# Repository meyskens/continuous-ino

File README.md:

Continuous Ino - CI server for Arduino  
======================================

Continuous Ino is a CI software designed to run unit tests in Arduino based hardware using frameworks like [arduinounit](https://github.com/mmurdoch/arduinounit).  
Continuous Ino will upload the code from a GitHub repository, run the tests and even emulates components. Continuous Ino itself runs on a Raspberry Pi, using a special designed PCB it's GPIO pins power an Arduino (nano) and is able to send and receive to the Arduino's interfaces. Both analog and digital signals are supported. 

## Background
Continuous Ino is developed for an international collaboration between TH Köln and Thomas More Geel. Since we have never seen a solution like this we've decided to open source our work under the GPL License following Arduino itself.

## Project by
- Ben De Breuker
- Maartje Eyskens
- Kristie Lim

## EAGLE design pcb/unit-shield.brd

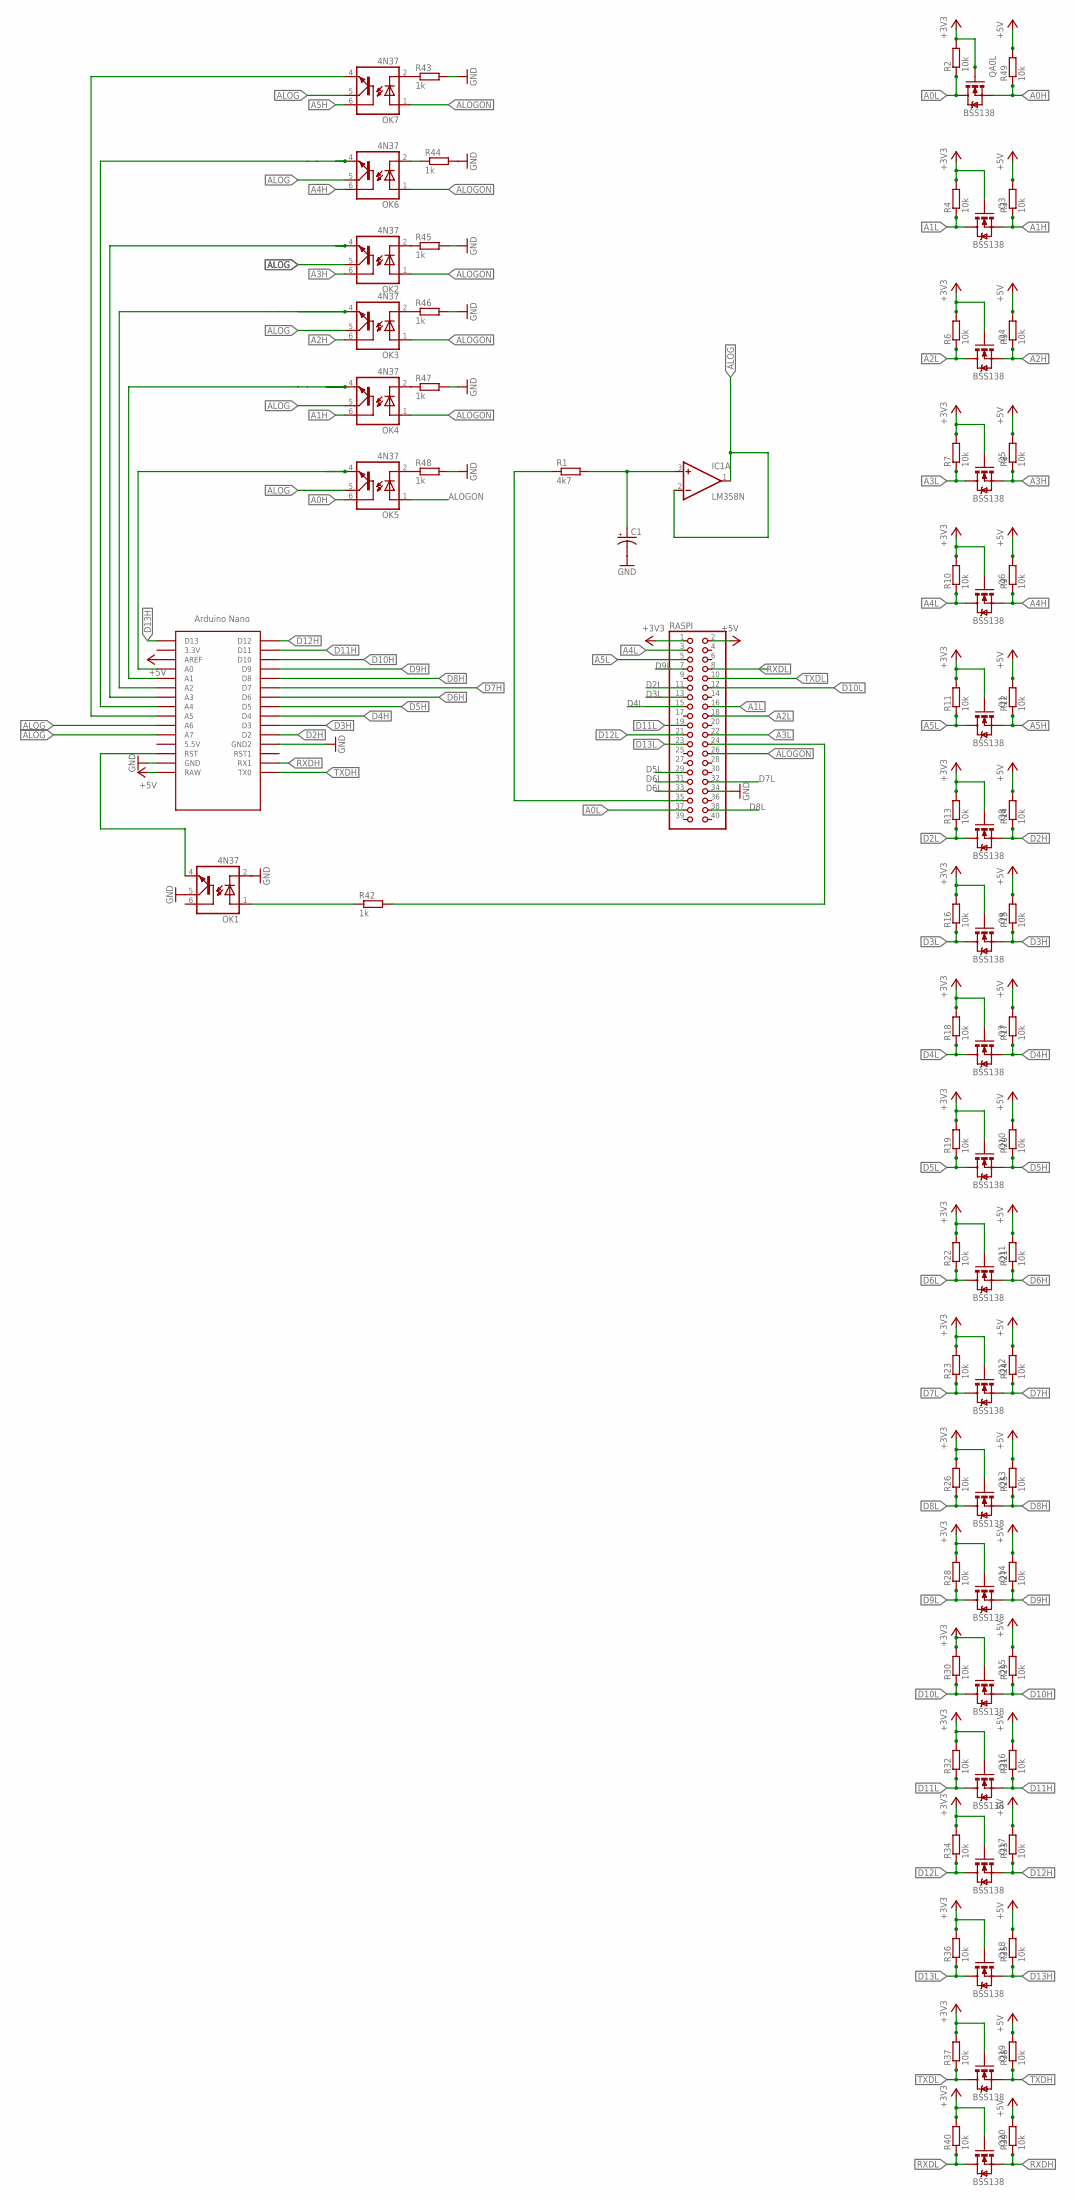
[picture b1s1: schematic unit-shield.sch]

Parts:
C1: CPOL-USB; PANASONIC_B
IC1: LM358N; DIL08
OK1, OK2, OK3, OK4, OK5, OK6, OK7: 4N37; DIL06
Q1, Q3, Q4, Q5, Q6, Q7, Q8, Q9, Q10, Q11, Q12, Q13, Q14, Q15, Q16, Q17, Q18, Q19, Q20: BSS138; SOT23-3
QA0L: BSS138; SOT23-3
R1: 4k7; M3216
R2, R3, R4, R5, R6, R7, R8, R9, R10, R11, R12, R13, R14, R15, R16, R17, R18, R19, R20, R21, R22, R23, R24, R25, R26, R27, R28, R29, R30, R31, R32, R33, R34, R35, R36, R37, R38, R39, R40, R49: 10k; M3216
R42, R43, R44, R45, R46, R47, R48: 1k; M3216
RASPI: PINHD-2X20; 2X20
U$1: NANO

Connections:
+3V3: Q1.1 (G), Q3.1 (G), Q4.1 (G), Q5.1 (G), Q6.1 (G), Q7.1 (G), Q8.1 (G), Q9.1 (G), Q10.1 (G), Q11.1 (G), Q12.1 (G), Q13.1 (G), Q14.1 (G), Q15.1 (G), Q16.1 (G), Q17.1 (G), Q18.1 (G), Q19.1 (G), Q20.1 (G), QA0L.1 (G), R2.2, R4.2, R6.2, R7.2, R10.2, R11.2, R13.2, R16.2, R18.2, R19.2, R22.2, R23.2, R26.2, R28.2, R30.2, R32.2, R34.2, R36.2, R37.2, R40.2, RASPI.1
+5V: R3.2, R5.2, R8.2, R9.2, R12.2, R14.2, R15.2, R17.2, R20.2, R21.2, R24.2, R25.2, R27.2, R29.2, R31.2, R33.2, R35.2, R38.2, R39.2, R49.2, RASPI.2, U$1.AREF, U$1.RAW
A0H: OK5.6 (BAS), QA0L.2 (S), R49.1
A0L: QA0L.3 (D), R2.1, RASPI.37
A1H: OK4.6 (BAS), Q3.2 (S), R3.1
A1L: Q3.3 (D), R4.1, RASPI.16
A2H: OK3.6 (BAS), Q4.2 (S), R5.1
A2L: Q4.3 (D), R6.1, RASPI.18
A3H: OK2.6 (BAS), Q5.2 (S), R8.1
A3L: Q5.3 (D), R7.1, RASPI.22
A4H: OK6.6 (BAS), Q6.2 (S), R9.1
A4L: Q6.3 (D), R10.1, RASPI.3
A5H: OK7.6 (BAS), Q1.2 (S), R12.1
A5L: Q1.3 (D), R11.1, RASPI.5
ALOG: IC1.1 (OUT), IC1.2 (-IN), OK2.5 (COL), OK3.5 (COL), OK4.5 (COL), OK5.5 (COL), OK6.5 (COL), OK7.5 (COL), U$1.A6, U$1.A7
ALOGON: OK2.1 (A), OK3.1 (A), OK4.1 (A), OK5.1 (A), OK6.1 (A), OK7.1 (A), RASPI.26
D2H: Q8.2 (S), R14.1, U$1.D2
D2L: Q8.3 (D), R13.1, RASPI.11
D3H: Q9.2 (S), R15.1, U$1.D3
D3L: Q9.3 (D), R16.1, RASPI.13
D4H: Q7.2 (S), R17.1, U$1.D4
D4L: Q7.3 (D), R18.1, RASPI.15
D5H: Q10.2 (S), R20.1, U$1.D5
D5L: Q10.3 (D), R19.1, RASPI.29
D6H: Q11.2 (S), R21.1, U$1.D6
D6L: Q11.3 (D), R22.1, RASPI.31, RASPI.33
D7H: Q12.2 (S), R24.1, U$1.D7
D7L: Q12.3 (D), R23.1, RASPI.32
D8H: Q13.2 (S), R25.1, U$1.D8
D8L: Q13.3 (D), R26.1, RASPI.38
D9H: Q14.2 (S), R27.1, U$1.D9
D9L: Q14.3 (D), R28.1, RASPI.7
D10H: Q15.2 (S), R29.1, U$1.D10
D10L: Q15.3 (D), R30.1, RASPI.12
D11H: Q16.2 (S), R31.1, U$1.D11
D11L: Q16.3 (D), R32.1, RASPI.19
D12H: Q17.2 (S), R33.1, U$1.D12
D12L: Q17.3 (D), R34.1, RASPI.21
D13H: Q18.2 (S), R35.1, U$1.D13
D13L: Q18.3 (D), R36.1, RASPI.23
GND: C1.-, OK1.2 (C), OK1.5 (COL), R43.2, R44.2, R45.2, R46.2, R47.2, R48.2, RASPI.34, U$1.GND, U$1.GND1 (GND2)
unnamed: OK1.4 (EMI), U$1.RST
unnamed: R42.2, RASPI.24
unnamed: OK7.2 (C), R43.1
unnamed: OK2.4 (EMI), U$1.A3
unnamed: OK3.4 (EMI), U$1.A2
unnamed: OK4.4 (EMI), U$1.A1
unnamed: OK5.4 (EMI), U$1.A0
unnamed: OK3.2 (C), R46.1
unnamed: OK7.4 (EMI), U$1.A5
unnamed: R1.1, RASPI.35
unnamed: OK6.4 (EMI), U$1.A4
unnamed: C1.+, IC1.3 (+IN), R1.2
unnamed: OK1.1 (A), R42.1
unnamed: OK6.2 (C), R44.1
unnamed: OK2.2 (C), R45.1
unnamed: OK4.2 (C), R47.1
unnamed: OK5.2 (C), R48.1
RXDH: Q20.2 (S), R39.1, U$1.RX1
RXDL: Q20.3 (D), R40.1, RASPI.8
TXDH: Q19.2 (S), R38.1, U$1.TX0
TXDL: Q19.3 (D), R37.1, RASPI.10
V+: IC1.8 (V+)
V-: IC1.4 (V-)

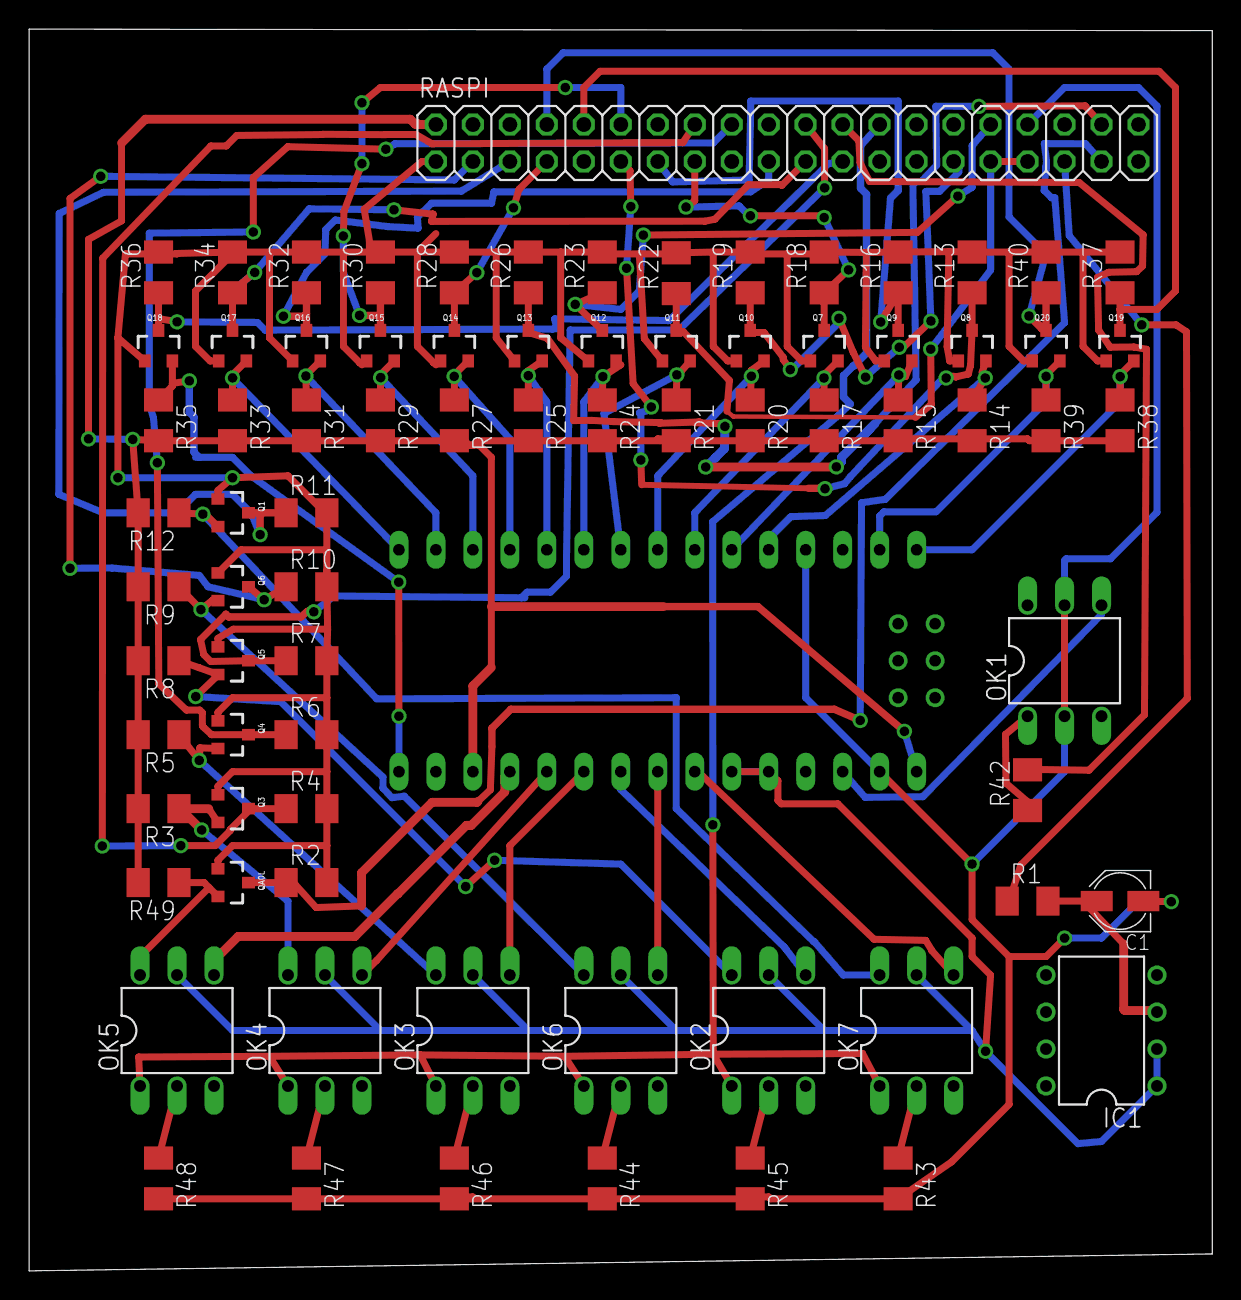
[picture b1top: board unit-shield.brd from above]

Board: 2 copper layers, 81.3 x 85.3 mm, 79 parts (0 on the bottom side), 62 nets.

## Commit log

2017-10-14 add container build
2017-10-14 fix typo
2017-10-14 use latest
2017-10-14 rm unneeded options
2017-10-14 add test build for go
2017-10-14 use langyage: go
2017-10-14 use latest go
2017-10-14 add --no-install-recommends
2017-10-14 add python-setuptools
2017-10-14 add wheel
2017-10-14 fix wrong name
2017-10-14 no arm64 till bugs fixed
2017-10-15 rm /src
2017-10-15 add server
2017-10-15 add readme
2017-10-15 add config
2017-10-15 add github client
2017-10-15 use cfg
2017-10-15 add webhook handling
2017-10-15 sett dummy commit status
2017-10-15 echo GOARCH
2017-10-15 correct exec path
2017-10-15 try to fix matrix
2017-10-15 redo vars
2017-10-16 add print error on invalid secret
2017-10-21 print secret
2017-10-21 rm debug log
2017-10-21 log more
2017-10-21 use after
2017-10-21 rm debug logs
2017-10-21 add build badge
2017-10-21 test clone and presence of build file
2017-10-21 lock mutex on push event
2017-10-21 fix clone + add tests
2017-10-21 add buildfile parser
2017-10-21 use parse in build
2017-10-21 add file to test
2017-10-21 add arduino model
2017-10-22 add database path
2017-10-22 open db file on launch
2017-10-22 add ability to run build tests
2017-10-22 add ino to travis
2017-10-22 sudo!
2017-10-22 typo fix
2017-10-22 sudo pip
2017-10-22 add build essential
2017-10-22 turns out I own an nano328
2017-10-22 upload the code to the arduino
2017-10-26 Go GPL to match libraries
2017-10-29 add baud
2017-10-29 fix test to have defaults
2017-10-29 add timeout
2017-10-29 fake cmd exec for test
2017-10-29 Add serialhandler
2017-10-29 use serialhandler when connecting to arduino serial
2017-10-29 use serial directly
2017-10-29 dep init
2017-10-29 rm dep
2017-10-29 use glide
2017-10-29 add extra go get?
2017-10-29 my mistake
2017-10-29 print output after done... DUH
2017-10-29 get errors from serial
2017-10-29 add storage to store runs in
2017-10-29 rm binary
2017-10-29 store runs in DB
2017-10-29 use new arduino
2017-10-29 comment mistake fix
2017-10-29 arduinoversion
2017-10-29 install ino from source
2017-10-29 get rid of ino
2017-10-29 oops we do GPL now
2017-10-29 add local build scrips
2017-10-29 fix no ca
2017-10-30 I wasn't fully awake...
2017-10-30 remove p from cpu name
2017-10-30 add port
2017-10-30 add error check to serialhandler
2017-10-30 fix default model
2017-10-30 use DefaultSubmoduleRecursionDepth
2017-10-30 rm depth
2017-10-30 More error words!
2017-10-30 Add test to check error finding
2017-10-30 log some more!
2017-10-30 add frontend
2017-10-30 save the travis file you idiot
2017-10-30 install yarn
2017-10-31 add node 8
2017-10-31 fix npm i
2017-10-31 rm app
2017-11-01 add get build api
2017-11-01 add get all runs
2017-11-01 add api to get all builds
2017-11-01 fix non handled error
2017-11-01 add sha
2017-11-01 add CORS
2017-11-01 Add name to static html
2017-11-01 add json tags
2017-11-01 list old builds first
2017-11-01 fix var misnaming
2017-11-01 add list builds
2017-11-01 add simple log viewer
2017-11-01 add running and errors to store
2017-11-01 store as []error
2017-11-01 add waiting for output
2017-11-01 move declare of outputList
2017-11-02 add build indicators
2017-11-02 use cosmo theme
2017-11-02 rm manifest
2017-11-02 rm unused import
2017-11-25 log arduino upload
2017-11-25 patch test
2017-12-28 add pcb
